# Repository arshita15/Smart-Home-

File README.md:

# Smart-Home-

Smart Home Environment Monitoring and Control System

In modern homes, maintaining a healthy and comfortable environment is crucial for well-being.
Traditional monitoring systems are often limited in functionality and require manual intervention.

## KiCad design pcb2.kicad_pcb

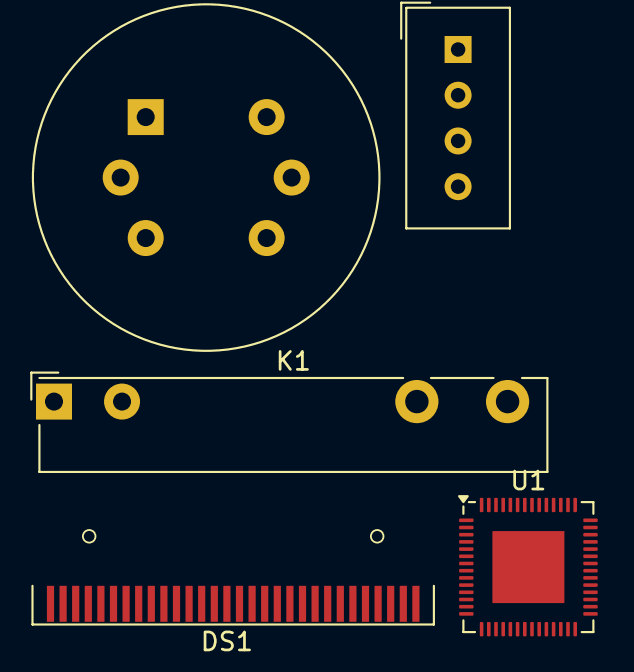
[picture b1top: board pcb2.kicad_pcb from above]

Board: 2 copper layers, 5 parts (0 on the bottom side), 5 nets, no tracks yet.

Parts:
DS1: OLED-128O064D
K1: Fujitsu_FTR-LYAA005x; Relay_SPST-NO_Fujitsu_FTR-LYAA005x_FormA_Vertical
U1: ESP32-S3; QFN-56-1EP_7x7mm_P0.4mm_EP4x4mm
U2: MQ-6
U3: DHT11; Aosong_DHT11_5.5x12.0_P2.54mm

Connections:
unnamed: DS1.29 (VLSS), K1.13, K1.A2, U1.43 (GPIO38), U1.45 (MTDO), U2.5 (VH-)
unnamed: DS1.8 (VSS), U1.44 (MTCK)
unnamed: DS1.1 (GND), DS1.30 (GND), U1.57 (GND), U3.4 (GND)
unnamed: K1.14, K1.A1, U1.15 (GPIO10), U1.55 (VDDA), U1.56 (VDDA)
unnamed: U1.2 (VDD3P3), U1.3 (VDD3P3)
